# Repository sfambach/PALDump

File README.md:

# PALDump – fork with a Mega 2560 shield

This is a fork of [rpocc/PALDump](https://github.com/rpocc/PALDump) by Dmitry Shtatnov. It adds a plug-on PCB (shield) for
the Arduino Mega 2560 with one 24-pin ZIF socket, so PALs can be dumped without a breadboard. The original description
follows below, unchanged.

## Shield

- **One 24-pin ZIF socket (0.3").** 24-pin PALs (PAL20L8) fill it. 20-pin PALs (PAL16L8, PAL10L8 and other
  combinatorial 20-pin types) go in **flush with pin 1** (lever side), the four contacts at the far end stay empty.
  Pin 24 is VCC for both sizes.
- **S2 "20/24".** Contact 10 is GND for a 20-pin PAL and an input for a 24-pin PAL; S2 switches it. Its second pole
  tells the firmware the type (D40), so no recompiling between PAL16L8 and PAL20L8.
- **S1 "PAL power".** Off: the socket is unpowered and the Arduino is held in reset, so all pins are high-impedance
  while you change the chip. On: the socket gets 5 V and the dump starts. Red LED = socket powered, green LED = dump
  running (D41).
- **Resistor arrays.** Every socket contact has a 270 Ω series resistor (3× DIP-16 isolated array). Contacts 15–23
  can carry PAL outputs and get a 1 kΩ to the probe line D39 (bussed SIP-10) for the tri-state detection.
- The firmware maps the socket contacts to the three port bytes the analysis works with (`PALDump.h`, port layer),
  so the dump is the same as with the original wiring. `PALDUMP_SHIELD 0` in `PALDump.h` restores the breadboard
  wiring.

| Socket contact | 20-pin PAL (S2 on 20) | 24-pin PAL (S2 on 24) | Arduino Mega |
|---|---|---|---|
| 1–8 | I1–I8 | I0–I7 | D22–D29 (PA0–PA7) |
| 9 | I9 | I8 | D37 (PC0) |
| 10 | GND (via S2) | I9 | D36 (PC1) via S2 |
| 11 | – | I10 | D35 (PC2) |
| 12 | – | GND | GND |
| 13 | – | I13 | D32 (PC5) |
| 14 | – | I11 | D34 (PC3) |
| 15 | I10 (pin 11) | O1 | A8 (PK0) |
| 16–22 | O1, IO2–IO7 (pins 12–18) | IO2–IO7, O8 | A9–A15 (PK1–PK7) |
| 23 | O8 (pin 19) | I12 | D33 (PC4) |
| 24 | VCC (pin 20) | VCC | 5 V via S1 |

Usage: S1 off, S2 to the PAL size, insert the PAL, open the serial monitor (115200 Bd, log to file), S1 on. The
analysis and the truth table run as described below; the green LED goes off when it is done.

Files:

- `hardware/shield/` – KiCad 7 project, schematic PDF/PNG, gerber ZIP, renders, DRC report
- `hardware/generator/` – Python scripts that generate schematic and board (`sh build.sh shield`, then
  `sh outputs.sh shield`; KiCad 7, Freerouting 1.9). The schematic wires are drawn by `router.py`.
- `hardware/lib/` – ZIF symbol with the PAL pin roles; Mega shield footprint from
  [Alarm-Siren/arduino-kicad-library](https://github.com/Alarm-Siren/arduino-kicad-library) (CC BY-SA 4.0)
- `test/sim/` – host build of the firmware against a simulated PAL; checks that shield and original wiring give
  the same dump (`sh test/sim/run.sh`)

Status: **not built yet** – the board and the shield firmware are untested on real hardware; the simulation passes.

### Parts

| Qty | Ref | Part |
|---|---|---|
| 1 | U1 | ZIF socket 24-pin, 0.3" narrow (e.g. 3M Textool 224-5248-00-0602J) |
| 3 | RN1–RN3 | Resistor array 8× 270 Ω isolated, DIP-16 (e.g. Bourns 4116R-1-271) |
| 1 | RN4 | Resistor array 9× 1 kΩ bussed, SIP-10 (e.g. Bourns 4610X-101-102) |
| 2 | S1, S2 | Slide switch DPDT, 2.54 mm (C&K JS202011CQN) |
| 2 | R1, R2 | Resistor 1 kΩ |
| 1 | D1 | LED 3 mm red |
| 1 | D2 | LED 3 mm green |
| 1 | C1 | Capacitor 100 nF |
| 1 | C2 | Electrolytic capacitor 10 µF |
| 1 set | – | Headers for the Mega: 1× 10, 5× 8, 1× 2×18 (male pin headers, or stacking headers) |

## Authors

- **Dmitry Shtatnov** (rpocc) – PALDump firmware and method – https://github.com/rpocc/PALDump
- **Stefan Fambach** (SteFam) – idea and concept of the shield build, review and testing – https://www.fambach.net
- **Claude** (Anthropic AI) – implementation of the shield build (schematic, PCB, firmware port layer and
  documentation), via Claude Code

## AI disclosure

The shield build in this fork is made with AI assistance. Stefan Fambach had the idea, set the concept and reviews
and tests every change; the implementation (schematic, PCB, firmware changes and documentation) is written largely by
Claude (Anthropic) via Claude Code. The original PALDump firmware is the work of Dmitry Shtatnov.

## Licence

- Firmware (`source/`): CC BY-NC-SA 4.0, as the original PALDump (see the header of `PALDump_2560.ino`). The shield
  changes are under the same licence.
- Shield hardware (`hardware/shield/`, `hardware/generator/`, `hardware/lib/paldump.kicad_sym`): CERN-OHL-S-2.0.
- Mega shield footprint/symbol (`hardware/lib/arduino-library*`): CC BY-SA 4.0, Alarm-Siren.

---

# Original README

# PALDump
Combinatorial Programmable Array Logic dumper for Arduino

Features:
 1. Detection of tri-state outputs using the dedicated probe pin.
 2. Analysis of outputs. It reads each output pin and counts occurunces of each state for all 65K/1M of input combinations, detects inputs, outputs, I/O or buffered outputs and builds a list of output functions per physical output and Output Enable.
 3. Analysis of inputs. It tests each input or I/O pin and detects if any change at this input doesn't affect output functions. Then it builds a table of usable inputs.
 4. It generates the optimized truth table (with excluded unused inputs) in Berkeley format and transfers it via Serial port. (USB/UART1 by default)

Requirements:
 1. An Arduino development board. MEGA2560 is recommended. Uno and other ATMEGA328 based boards aren't supported!
 2. 3x complete I/O ports (7..0), which aren't shared with Serial.
 3. 1x additional I/O pin for probe
 4. A breadboard with a set of jumper wires
 5. 25x Dupont/compatible Male-Male wires
 6. 8x thru-hole resistors of 220..270 Ohms
 7. 8x thru-hole resistors or one-to-many resistor array of 1..1.5 KOhm
 8. A terminal program which can save serial communication log to a file. (Arduino IDE 2.0+ doesn't allow exporting or copying of the Serial Monitor output, so PuTTY is recommended)
 9. Installed Espresso Logic Minimizer. (Free)
10. A CPLD development software such as Atmel WinCUPL for generating the .jed files

Usage:
 1. Connect the PLA chip to the Arduino as shown on the schematic (See PALDump.h)
 2. Set the constant PALDump::PALType globalPALType to PAL16L8 or PAL20L8
 3. Recompile and upload the project into Aruino board.
 4. Connect with the Arduino serial port using a terminal program and save the full log to a text file.
 5. Clean the header if needed and feed the file to Espresso using the following command:

    espresso -Dexact -Dmany -o eqntott inputfile.pld > outputfile.pld

 6. Analyze and reformat the output in order to use it for designing your own clone of PLA using CPLD design software of your choice. (Invert boolean functions for outputs, keep for .OE, remove input terms for buffered outputs, which are duplicated in .OE equations, etc)

Precautions:
*  Serial communication at 115200 bps is slow for transferring thousands of text lines. It can take up to 200 seconds for transferring 65K entries and up to 1 hour (!) for 1M entries, so program does it best in advance to exclude unneeded inputs and outputs from the truth table which halfs its size with each excluded input . Analysis of PAL16xx usually takes up to 20 seconds while full analysis of PAL20xx may take 16 times more, but eventually it saves up to 10 times more time. Using faster serial communication is also adviced.
*  It's recommended to read several copies of truth table and compare them using fc or another file compare utility to detect errors. Automatic optional error-correction will be added later, but it's expected to consume more time.
*  This tool isn't designed as a blind push-button solution, although most of hardwork is performed in fully automatic mode along with Espresso. The output still needs evaluation with a certain degree of scepticism and common sense.

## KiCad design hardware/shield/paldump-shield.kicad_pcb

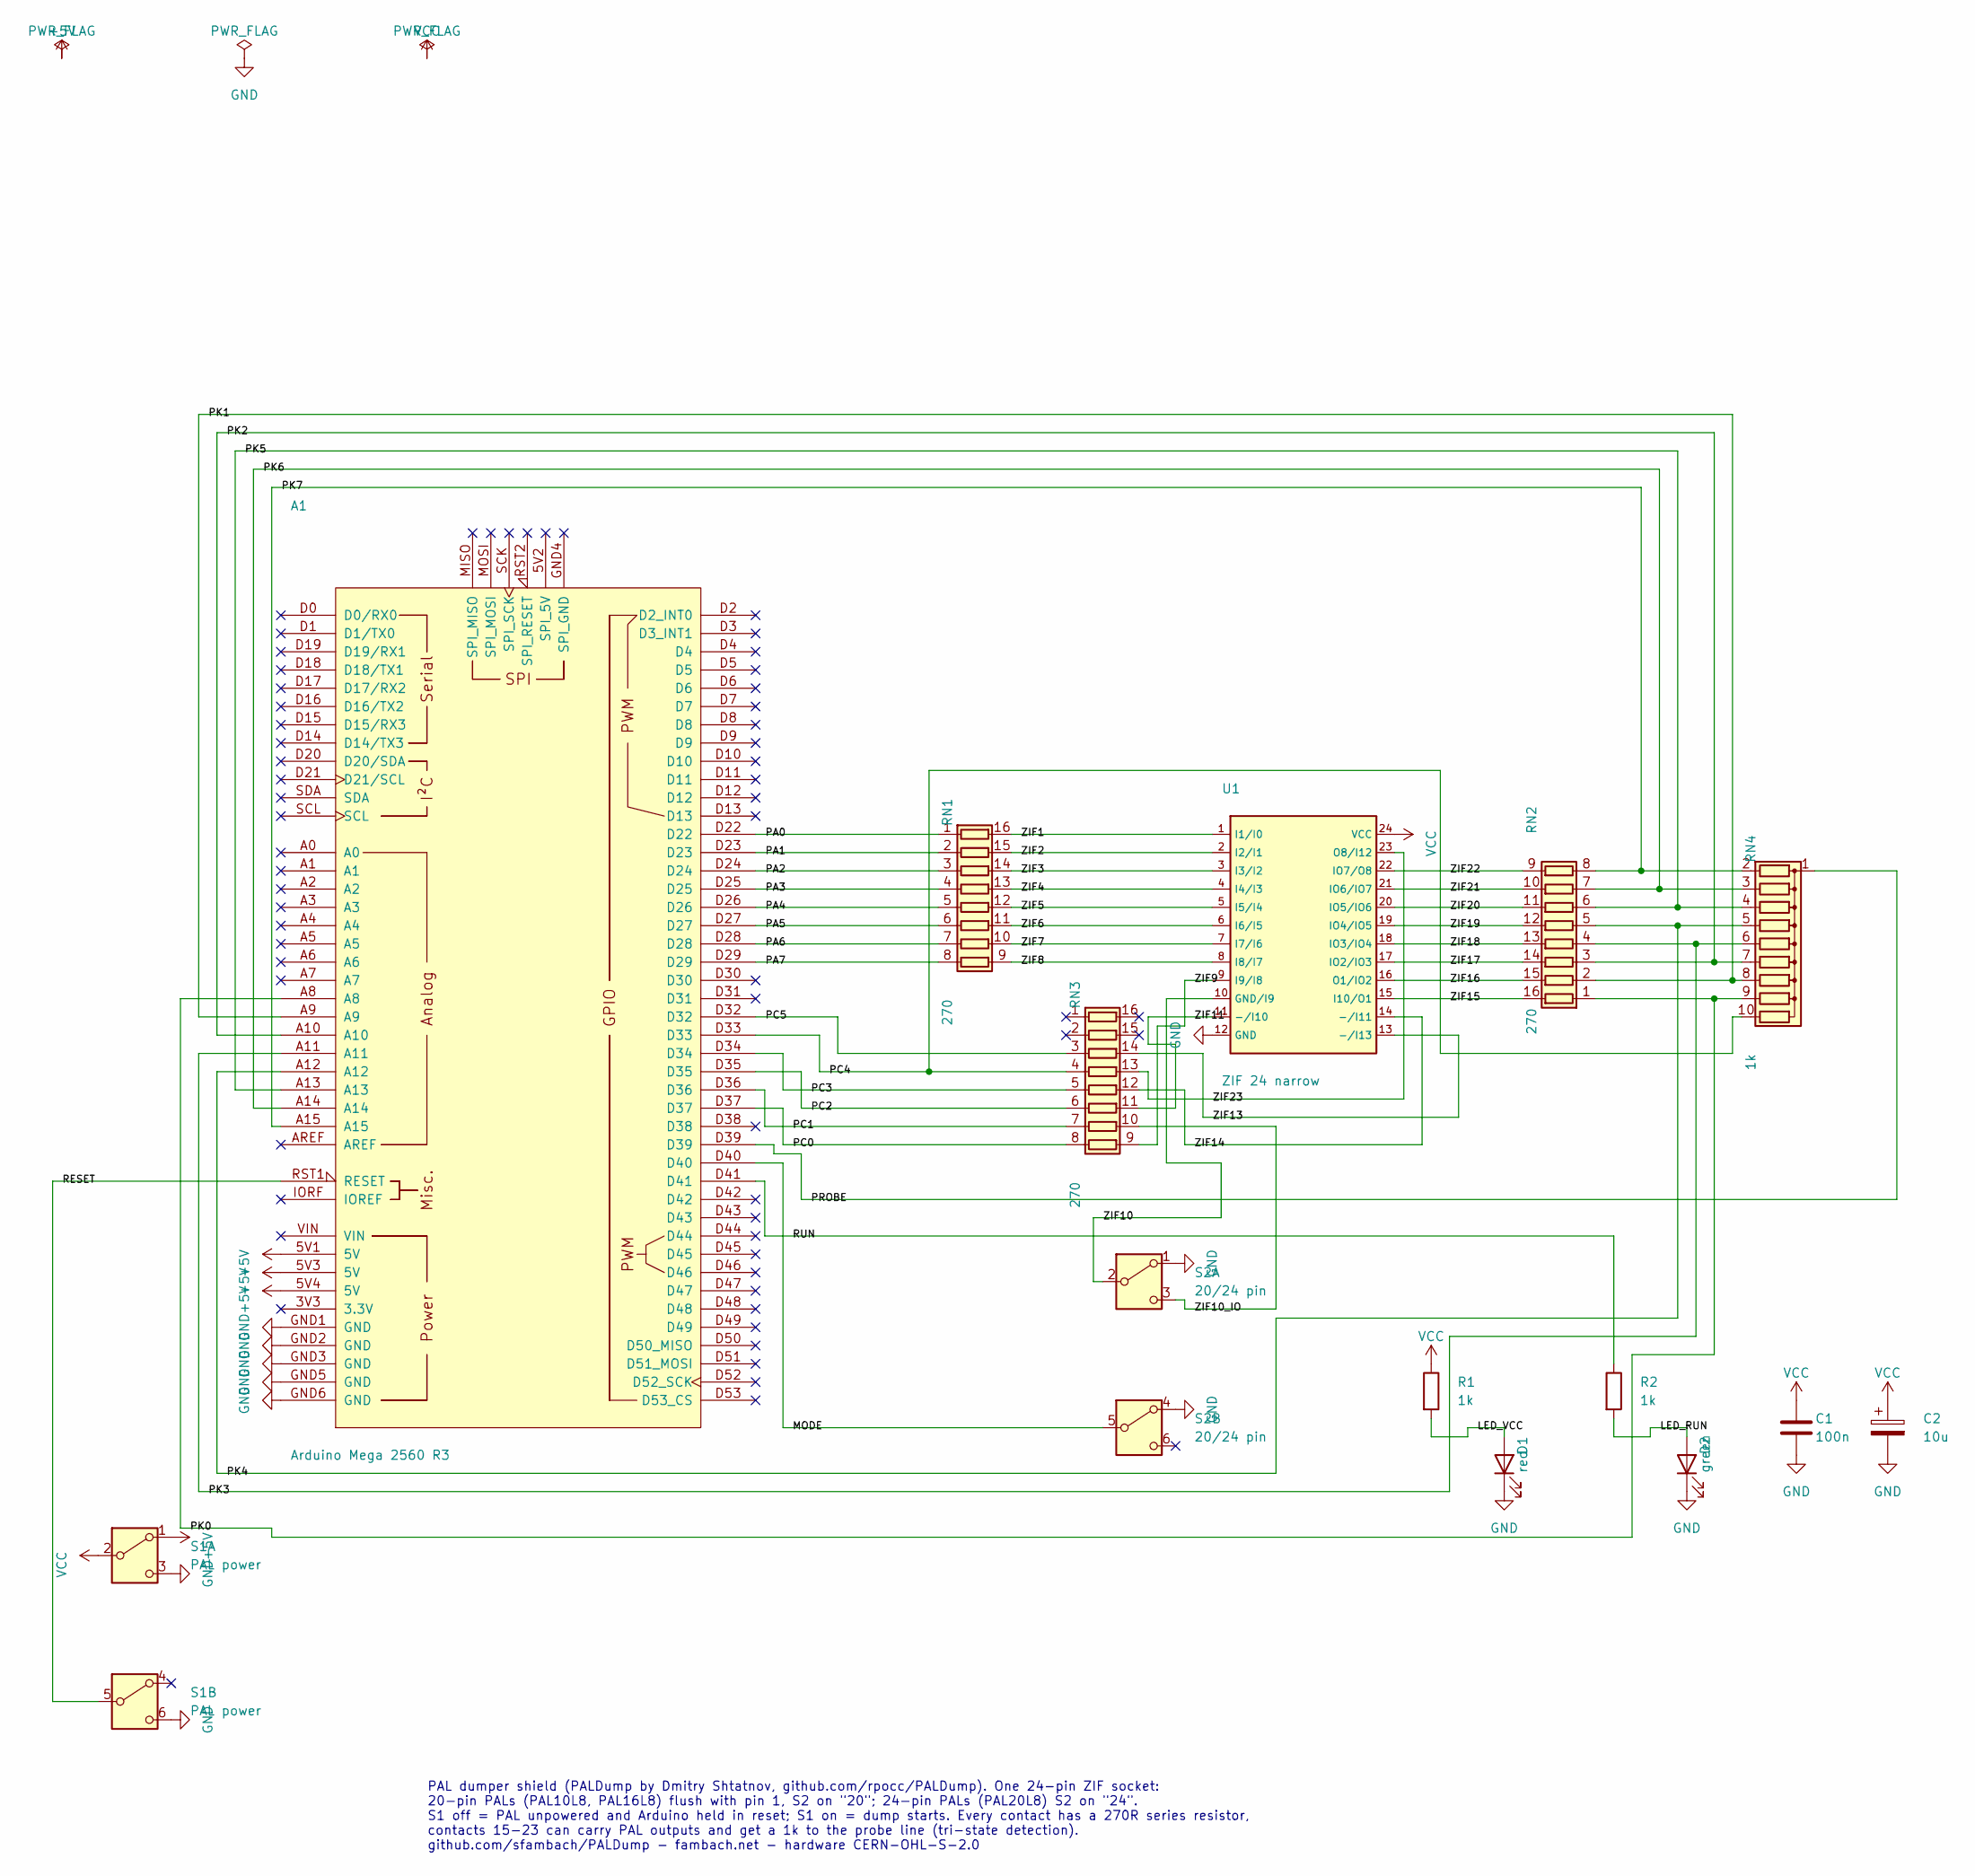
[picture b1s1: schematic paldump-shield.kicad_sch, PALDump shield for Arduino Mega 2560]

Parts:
A1: Arduino Mega 2560 R3; Arduino_Mega2560_R3_Shield
C1: 100n; C_Disc_D5.0mm_W2.5mm_P5.00mm
C2: 10u; CP_Radial_D5.0mm_P2.00mm
D1: red; LED_D3.0mm
D2: green; LED_D3.0mm
R1, R2: 1k; R_Axial_DIN0207_L6.3mm_D2.5mm_P7.62mm_Horizontal
RN1, RN2, RN3: 270; DIP-16_W7.62mm_Socket
RN4: 1k; R_Array_SIP10
S1: PAL power; SW_CK_JS202011CQN_DPDT_Straight
S2: 20/24 pin; SW_CK_JS202011CQN_DPDT_Straight
U1: ZIF 24 narrow; DIP_Socket-24_W4.3_W5.08_W7.62_W10.16_W10.9_3M_224-5248-00-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

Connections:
+5V: A1.5V1 (5V), A1.5V3 (5V), A1.5V4 (5V), S1.1 (A)
/LED_RUN: D2.2 (A), R2.2
/LED_VCC: D1.2 (A), R1.2
/MODE: A1.D40, S2.5 (B)
/PA0: A1.D22, RN1.1 (R1.1)
/PA1: A1.D23, RN1.2 (R2.1)
/PA2: A1.D24, RN1.3 (R3.1)
/PA3: A1.D25, RN1.4 (R4.1)
/PA4: A1.D26, RN1.5 (R5.1)
/PA5: A1.D27, RN1.6 (R6.1)
/PA6: A1.D28, RN1.7 (R7.1)
/PA7: A1.D29, RN1.8 (R8.1)
/PC0: A1.D37, RN3.8 (R8.1)
/PC1: A1.D36, RN3.7 (R7.1)
/PC2: A1.D35, RN3.6 (R6.1)
/PC3: A1.D34, RN3.5 (R5.1)
/PC4: A1.D33, RN3.4 (R4.1), RN4.10 (R9)
/PC5: A1.D32, RN3.3 (R3.1)
/PK0: A1.A8, RN2.1 (R1.1), RN4.9 (R8)
/PK1: A1.A9, RN2.2 (R2.1), RN4.8 (R7)
/PK2: A1.A10, RN2.3 (R3.1), RN4.7 (R6)
/PK3: A1.A11, RN2.4 (R4.1), RN4.6 (R5)
/PK4: A1.A12, RN2.5 (R5.1), RN4.5 (R4)
/PK5: A1.A13, RN2.6 (R6.1), RN4.4 (R3)
/PK6: A1.A14, RN2.7 (R7.1), RN4.3 (R2)
/PK7: A1.A15, RN2.8 (R8.1), RN4.2 (R1)
/PROBE: A1.D39, RN4.1 (common)
/RESET: A1.RST1 (RESET), S1.5 (B)
/RUN: A1.D41, R2.1
/VCC: C1.1, C2.1, R1.1, S1.2 (B), U1.24 (VCC)
/ZIF1: RN1.16 (R1.2), U1.1 (I1/I0)
/ZIF2: RN1.15 (R2.2), U1.2 (I2/I1)
/ZIF3: RN1.14 (R3.2), U1.3 (I3/I2)
/ZIF4: RN1.13 (R4.2), U1.4 (I4/I3)
/ZIF5: RN1.12 (R5.2), U1.5 (I5/I4)
/ZIF6: RN1.11 (R6.2), U1.6 (I6/I5)
/ZIF7: RN1.10 (R7.2), U1.7 (I7/I6)
/ZIF8: RN1.9 (R8.2), U1.8 (I8/I7)
/ZIF9: RN3.9 (R8.2), U1.9 (I9/I8)
/ZIF10: S2.2 (B), U1.10 (GND/I9)
/ZIF10_IO: RN3.10 (R7.2), S2.3 (C)
/ZIF11: RN3.11 (R6.2), U1.11 (-/I10)
/ZIF13: RN3.14 (R3.2), U1.13 (-/I13)
/ZIF14: RN3.12 (R5.2), U1.14 (-/I11)
/ZIF15: RN2.16 (R1.2), U1.15 (I10/O1)
/ZIF16: RN2.15 (R2.2), U1.16 (O1/IO2)
/ZIF17: RN2.14 (R3.2), U1.17 (IO2/IO3)
/ZIF18: RN2.13 (R4.2), U1.18 (IO3/IO4)
/ZIF19: RN2.12 (R5.2), U1.19 (IO4/IO5)
/ZIF20: RN2.11 (R6.2), U1.20 (IO5/IO6)
/ZIF21: RN2.10 (R7.2), U1.21 (IO6/IO7)
/ZIF22: RN2.9 (R8.2), U1.22 (IO7/O8)
/ZIF23: RN3.13 (R4.2), U1.23 (O8/I12)
GND: A1.GND1 (GND), A1.GND2 (GND), A1.GND3 (GND), A1.GND5 (GND), A1.GND6 (GND), C1.2, C2.2, D1.1 (K), D2.1 (K), S1.3 (C), S1.6 (C), S2.1 (A), S2.4 (A), U1.12 (GND)

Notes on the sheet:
PAL dumper shield (PALDump by Dmitry Shtatnov, github.com/rpocc/PALDump). One 24-pin ZIF socket: 20-pin PALs (PAL10L8, PAL16L8) flush with pin 1, S2 on "20"; 24-pin PALs (PAL20L8) S2 on "24". S1 off = PAL unpowered and Arduino held in reset; S1 on = dump starts. Every contact has a 270R series resi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

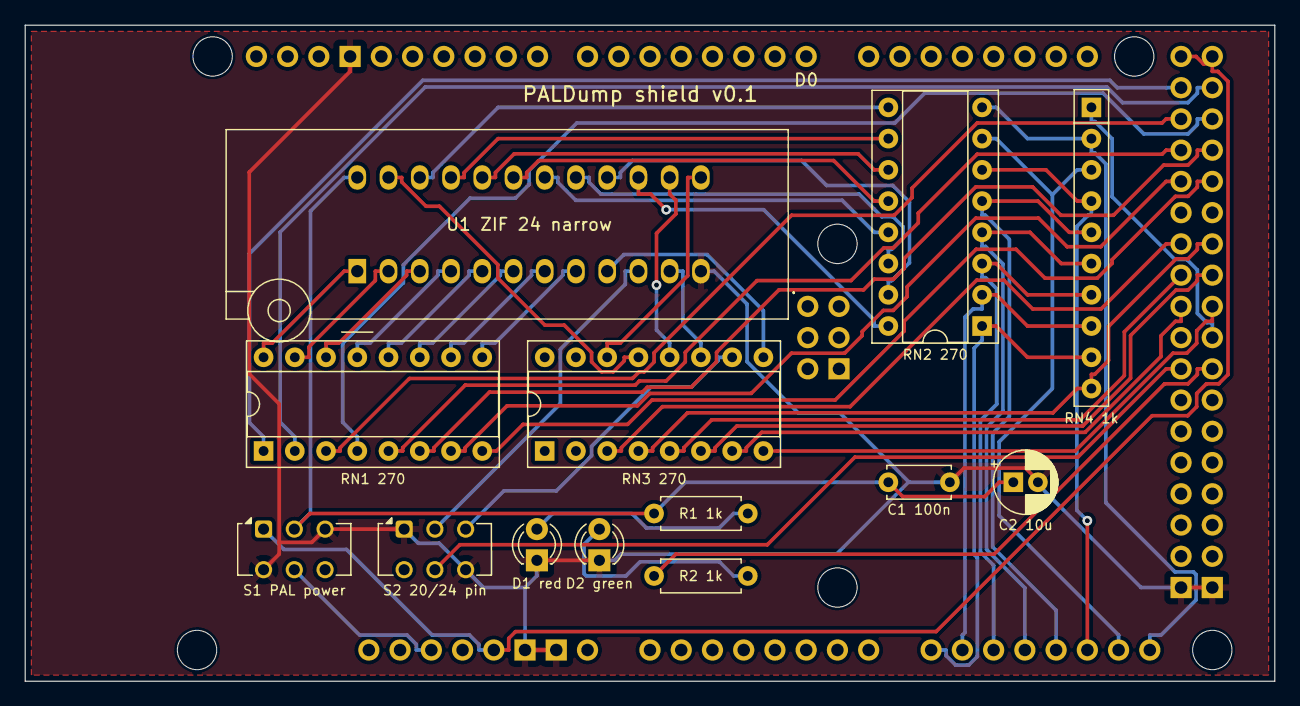
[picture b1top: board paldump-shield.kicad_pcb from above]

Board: 2 copper layers, 101.6 x 53.3 mm, 14 parts (0 on the bottom side), 54 nets.

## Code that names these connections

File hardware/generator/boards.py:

# Netlist and placement of the PALDump shield for the Arduino Mega 2560.
# Pin map as in the firmware (source/PALDump_2560/PALDump.cpp, class PALPorts):
#   ZIF 1-8 = PA0-PA7 (D22-D29), ZIF 9/10/11/14/23/13 = PC0-PC5 (D37-D32), ZIF 15-22 = PK0-PK7 (A8-A15),
#   probe = PG2 (D39), 20/24 switch = PG1 (D40), RUN LED = PG0 (D41).
# A 20-pin PAL sits flush with pin 1 of the 24-pin ZIF socket, so VCC is contact 24 for both sizes; contact 10 is GND for
# a 20-pin PAL and an input for a 24-pin PAL, switched by S2.
NC = None
POWER = {'+5V', 'GND', 'VCC'}

RPACK = 'Package_DIP:DIP-16_W7.62mm_Socket'
SIP10 = 'Resistor_THT:R_Array_SIP10'
ZIF = 'Socket:DIP_Socket-24_W4.3_W5.08_W7.62_W10.16_W10.9_3M_224-5248-00-0602J'
DPDT = 'Button_Switch_THT:SW_CK_JS202011CQN_DPDT_Straight'
R = 'Resistor_THT:R_Axial_DIN0207_L6.3mm_D2.5mm_P7.62mm_Horizontal'
LED = 'LED_THT:LED_D3.0mm'
C100N = 'Capacitor_THT:C_Disc_D5.0mm_W2.5mm_P5.00mm'
C10U = 'Capacitor_THT:CP_Radial_D5.0mm_P2.00mm'

UNO_PINS = ['3V3', '5V1', '5V2', 'A0', 'A1', 'A2', 'A3', 'A4', 'A5', 'AREF', 'D0', 'D1', 'D10', 'D11', 'D12', 'D13', 'D2', 'D3',
            'D4', 'D5', 'D6', 'D7', 'D8', 'D9', 'GND1', 'GND2', 'GND3', 'GND4', 'IORF', 'MISO', 'MOSI', 'RST1', 'RST2', 'SCK',
            'SCL', 'SDA', 'VIN']
MEGA_PINS = UNO_PINS + ['5V3', '5V4', 'A6', 'A7', 'A8', 'A9', 'A10', 'A11', 'A12', 'A13', 'A14', 'A15', 'GND5', 'GND6'] + \
    ['D%d' % i for i in range(14, 54)]

# ZIF contact -> port line; the series resistor sits between the two.
LINES = {**{s: 'PA%d' % (s - 1) for s in range(1, 9)},
         9: 'PC0', 10: 'PC1', 11: 'PC2', 14: 'PC3', 23: 'PC4', 13: 'PC5',
         **{s: 'PK%d' % (s - 15) for s in range(15, 23)}}
PROBED = ['PK%d' % i for i in range(8)] + ['PC4']  # lines that can carry a PAL output

mega = {'5V1': '+5V', '5V3': '+5V', '5V4': '+5V', 'GND1': 'GND', 'GND2': 'GND', 'GND3': 'GND', 'GND5': 'GND',
        'GND6': 'GND', 'RST1': 'RESET', 'D39': 'PROBE', 'D40': 'MODE', 'D41': 'RUN'}
for i in range(8):
    mega['D%d' % (22 + i)] = 'PA%d' % i
    mega['D%d' % (37 - i)] = 'PC%d' % i if i < 6 else NC
    mega['A%d' % (8 + i)] = 'PK%d' % i


def zif_net(s):
    return 'ZIF10_IO' if s == 10 else 'ZIF%d' % s


def rpack(pairs):
    """R_Pack08: resistor k between pin k (port side) and pin 17-k (socket side); pairs = 8 x (port, socket) or None."""
    conn = {}
    for k, pr in enumerate(pairs, 1):
        conn[str(k)], conn[str(17 - k)] = pr if pr else (NC, NC)
    return conn


zif = {'12': 'GND', '24': 'VCC', **{str(s): 'ZIF%d' % s for s in LINES}}
rn1 = rpack([('PA%d' % i, 'ZIF%d' % (i + 1)) for i in range(8)])
rn2 = rpack([('PK%d' % i, 'ZIF%d' % (15 + i)) for i in range(8)])
by_port = {v: k for k, v in LINES.items()}
rn3 = rpack([None, None] + [('PC%d' % i, zif_net(by_port['PC%d' % i])) for i in (5, 4, 3, 2, 1, 0)])
rn4 = {'1': 'PROBE', **{str(k + 2): 'PK%d' % (7 - k) for k in range(8)}, '10': 'PC4'}

# Schematic: (lib_id, value, footprint, (x, y), pin -> net)
PARTS = {
    'A1': ('arduino-library:Arduino_Mega2560_R3_Shield', 'Arduino Mega 2560 R3', 'arduino-library:Arduino_Mega2560_R3_Shield',
           (88.9, 152.4), {n: mega.get(n) for n in MEGA_PINS}),
    'RN1': ('Device:R_Pack08', '270', RPACK, (152.4, 138.43), rn1),
    'RN3': ('Device:R_Pack08', '270', RPACK, (170.18, 163.83), rn3),
    'U1': ('paldump:ZIF24_PAL', 'ZIF 24 narrow', ZIF, (198.12, 142.24), zif),
    'RN2': ('Device:R_Pack08', '270', RPACK, (233.68, 140.97), rn2),
    'RN4': ('Device:R_Network09', '1k', SIP10, (264.16, 143.51), rn4),
    'S2': ('Switch:SW_DPDT_x2', '20/24 pin', DPDT, (175.26, 190.5),
           {'1': 'GND', '2': 'ZIF10', '3': 'ZIF10_IO', '4': 'GND', '5': 'MODE', '6': NC}),
    'S1': ('Switch:SW_DPDT_x2', 'PAL power', DPDT, (35.56, 228.6),
           {'1': '+5V', '2': 'VCC', '3': 'GND', '4': NC, '5': 'RESET', '6': 'GND'}),
    'R1': ('Device:R', '1k', R, (215.9, 205.74), {'1': 'VCC', '2': 'LED_VCC'}),
    'D1': ('Device:LED', 'red', LED, (226.06, 215.9), {'1': 'GND', '2': 'LED_VCC'}),
    'R2': ('Device:R', '1k', R, (241.3, 205.74), {'1': 'RUN', '2': 'LED_RUN'}),
    'D2': ('Device:LED', 'green', LED, (251.46, 215.9), {'1': 'GND', '2': 'LED_RUN'}),
    'C1': ('Device:C', '100n', C100N, (266.7, 210.82), {'1': 'VCC', '2': 'GND'}),
    'C2': ('Device:C_Polarized', '10u', C10U, (279.4, 210.82), {'1': 'VCC', '2': 'GND'}),
}
SCH = dict(
    rot={'RN1': 270, 'RN3': 270, 'RN2': 90, 'RN4': 270, 'D1': 90, 'D2': 90},
    units={'S2': [(175.26, 190.5), (175.26, 210.82)], 'S1': [(35.56, 228.6), (35.56, 248.92)]},
    order=['RUN', 'MODE', 'RESET', 'PROBE', 'ZIF10', 'ZIF10_IO'],
)

X0, Y0 = 100, 153.34  # origin of the shield footprint = lower left corner of the Arduino

SHIELD = dict(
    name='paldump-shield',
    title='PALDump shield for Arduino Mega 2560',
    note='PAL dumper shield (PALDump by Dmitry Shtatnov, github.com/rpocc/PALDump). One 24-pin ZIF socket:\n'
         '20-pin PALs (PAL10L8, PAL16L8) flush with pin 1, S2 on "20"; 24-pin PALs (PAL20L8) S2 on "24".\n'
         'S1 off = PAL unpowered and Arduino held in reset; S1 on = dump starts. Every contact has a 270R series resistor,\n'
         'contacts 15-23 can carry PAL outputs and get a 1k to the probe line (tri-state detection).\n'
         'github.com/sfambach/PALDump - fambach.net - hardware CERN-OHL-S-2.0',
    power=['+5V', 'GND', 'VCC'],
    board=(X0, Y0 - 53.34, X0 + 101.6, Y0),
    parts=PARTS, sch=SCH,
    # The Mega's ICSP header pokes through the shield (pads stay, unconnected); keep its area free.
    place={
        'A1': ('origin', (X0, Y0), 0),
        'U1': ('at', (127.0, 120.0), 90),
        'RN1': ('at', (119.38, 134.62), 90),
        'RN3': ('at', (142.24, 134.62), 90),
        'RN2': ('at', (177.8, 124.46), 180),
        'RN4': ('at', (186.69, 106.68), 270),
        'S1': ('at', (119.38, 140.97), 0),
        'S2': ('at', (130.81, 140.97), 0),
        'D1': ('pads', (141.605, 143.51), (141.605, 140.97)),
        'D2': ('pads', (146.685, 143.51), (146.685, 140.97)),
        'R1': ('pads', (151.13, 139.7), (158.75, 139.7)),
        'R2': ('pads', (151.13, 144.78), (158.75, 144.78)),
        'C1': ('pads', (170.18, 137.16), (175.18, 137.16)),
        'C2': ('pads', (180.34, 137.16), (182.34, 137.16)),
    },
    texts=[('PALDump shield v0.1', 150.0, 105.6, 1.2)],
    btexts=[('PALDump shield v0.1 - fambach.net', 150, 125, 1.0), ('github.com/sfambach/PALDump', 150, 127.5, 0.8),
            ('CERN-OHL-S-2.0', 150, 129.6, 0.8)],
)

BOARDS = {'shield': SHIELD}
